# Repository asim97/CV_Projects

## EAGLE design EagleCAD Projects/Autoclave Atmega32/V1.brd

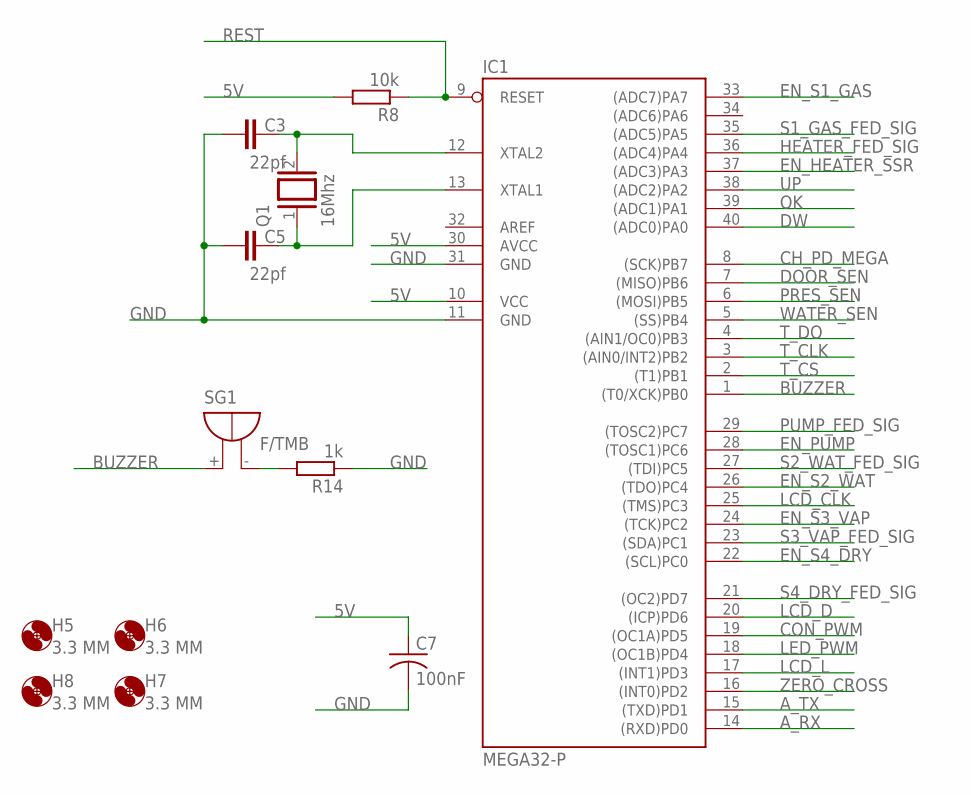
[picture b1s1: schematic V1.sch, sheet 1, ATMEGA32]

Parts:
C3, C5: 22pf; C050-030X075
C7: 100nF; C050-035X075
H5, H6, H7, H8: 3.3 MM; 3,3
IC1: MEGA32-P; DIL40
Q1: 16Mhz; QS
R8: 10k; 0207/10
R14: 1k; 0207/10
SG1: F/TMB

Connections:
5V: C7.1, IC1.10 (VCC), IC1.30 (AVCC), R8.2; also elsewhere on the board
A_RX: IC1.14 ((RXD)PD0); also elsewhere on the board
A_TX: IC1.15 ((TXD)PD1); also elsewhere on the board
BUZZER: IC1.1 ((T0/XCK)PB0), SG1.+
CH_PD_MEGA: IC1.8 ((SCK)PB7); also elsewhere on the board
CON_PWM: IC1.19 ((OC1A)PD5); also elsewhere on the board
DOOR_SEN: IC1.7 ((MISO)PB6); also elsewhere on the board
DW: IC1.40 ((ADC0)PA0); also elsewhere on the board
EN_HEATER_SSR: IC1.37 ((ADC3)PA3); also elsewhere on the board
EN_PUMP: IC1.28 ((TOSC1)PC6); also elsewhere on the board
EN_S1_GAS: IC1.33 ((ADC7)PA7); also elsewhere on the board
EN_S2_WAT: IC1.26 ((TDO)PC4); also elsewhere on the board
EN_S3_VAP: IC1.24 ((TCK)PC2); also elsewhere on the board
EN_S4_DRY: IC1.22 ((SCL)PC0); also elsewhere on the board
GND: C3.1, C5.1, C7.2, IC1.11 (GND), IC1.31 (GND), R14.1; also elsewhere on the board
HEATER_FED_SIG: IC1.36 ((ADC4)PA4); also elsewhere on the board
LCD_CLK: IC1.25 ((TMS)PC3); also elsewhere on the board
LCD_D: IC1.20 ((ICP)PD6); also elsewhere on the board
LCD_L: IC1.17 ((INT1)PD3); also elsewhere on the board
LED_PWM: IC1.18 ((OC1B)PD4); also elsewhere on the board
unnamed: C5.2, IC1.13 (XTAL1), Q1.1
unnamed: C3.2, IC1.12 (XTAL2), Q1.2
unnamed: R14.2, SG1.-
OK: IC1.39 ((ADC1)PA1); also elsewhere on the board
PRES_SEN: IC1.6 ((MOSI)PB5); also elsewhere on the board
PUMP_FED_SIG: IC1.29 ((TOSC2)PC7); also elsewhere on the board
REST: IC1.9 (RESET), R8.1; also elsewhere on the board
S1_GAS_FED_SIG: IC1.35 ((ADC5)PA5); also elsewhere on the board
S2_WAT_FED_SIG: IC1.27 ((TDI)PC5); also elsewhere on the board
S3_VAP_FED_SIG: IC1.23 ((SDA)PC1); also elsewhere on the board
S4_DRY_FED_SIG: IC1.21 ((OC2)PD7); also elsewhere on the board
T_CLK: IC1.3 ((AIN0/INT2)PB2); also elsewhere on the board
T_CS: IC1.2 ((T1)PB1); also elsewhere on the board
T_DO: IC1.4 ((AIN1/OC0)PB3); also elsewhere on the board
UP: IC1.38 ((ADC2)PA2); also elsewhere on the board
WATER_SEN: IC1.5 ((SS)PB4); also elsewhere on the board
ZERO_CROSS: IC1.16 ((INT0)PD2); also elsewhere on the board

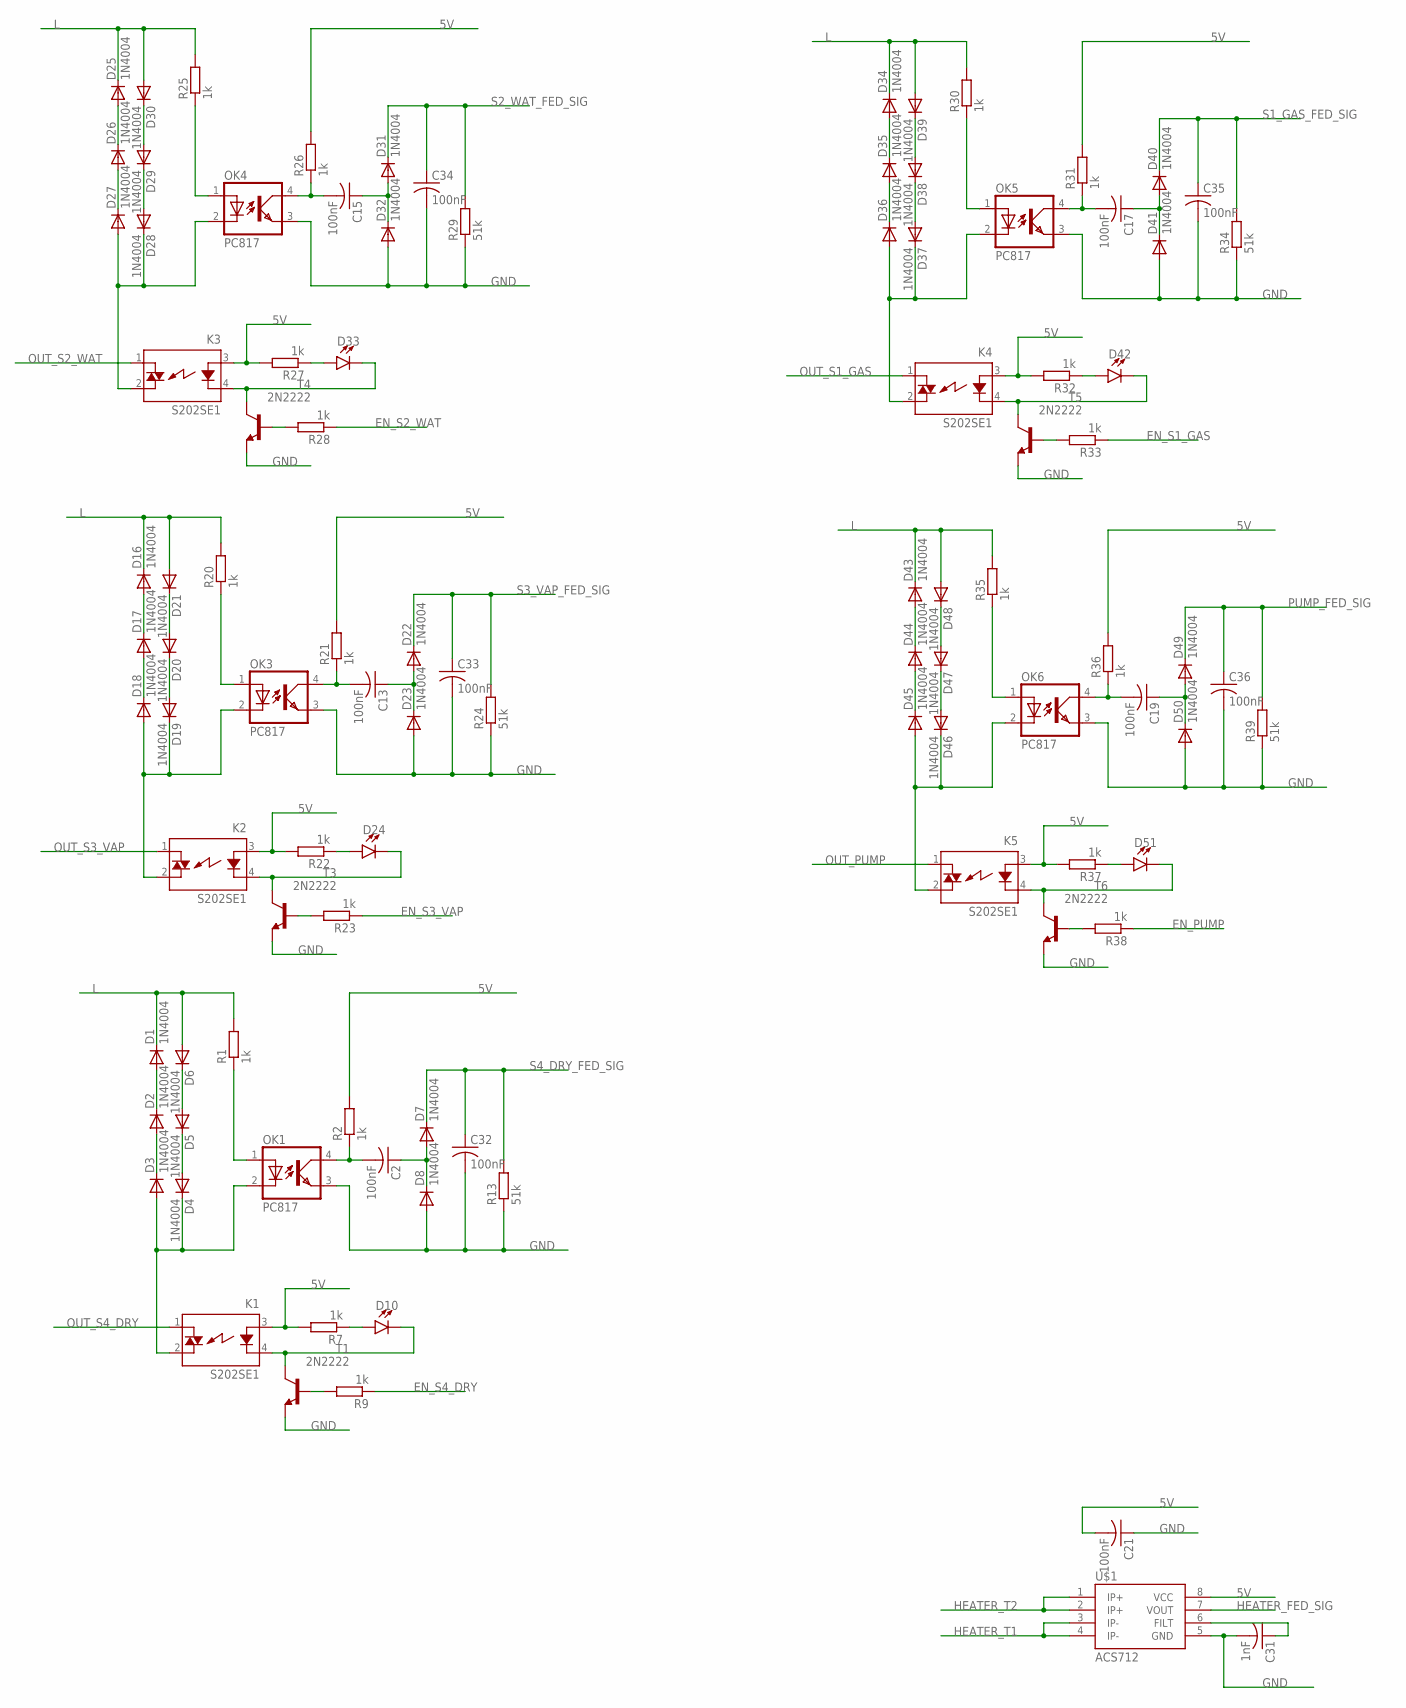
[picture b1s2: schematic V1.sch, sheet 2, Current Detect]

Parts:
C2, C13, C15, C17, C19, C21, C32, C33, C34, C35, C36: 100nF; C050-035X075
C31: 1nF; C050-035X075
D1, D2, D3, D4, D5, D6, D7, D8, D16, D17, D18, D19, D20, D21, D22, D23, D25, D26, D27, D28, D29, D30, D31, D32, D34, D35, D36, D37, D38, D39, D40, D41, D43, D44, D45, D46, D47, D48, D49, D50: 1N4004; DO41-10
D10, D24, D33, D42, D51: LED5MM; LED_5MM
K1, K2, K3, K4, K5: S202SE1; S2XXEX
OK1, OK3, OK4, OK5, OK6: PC817; DIL04
R1, R2, R7, R9, R20, R21, R22, R23, R25, R26, R27, R28, R30, R31, R32, R33, R35, R36, R37, R38: 1k; 0207/10
R13, R24, R29, R34, R39: 51k; 0207/10
T1, T3, T4, T5, T6: 2N2222; TO92-EBC-OVAL
U$1: ACS712; SO08

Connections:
5V: C21.2, K1.3 (A), K2.3 (A), K3.3 (A), K4.3 (A), K5.3 (A), R2.2, R7.2, R21.2, R22.2, R26.2, R27.2, R31.2, R32.2, R36.2, R37.2, U$1.8 (VCC); also elsewhere on the board
EN_PUMP: R38.1; also elsewhere on the board
EN_S1_GAS: R33.1; also elsewhere on the board
EN_S2_WAT: R28.1; also elsewhere on the board
EN_S3_VAP: R23.1; also elsewhere on the board
EN_S4_DRY: R9.1; also elsewhere on the board
GND: C21.1, C31.2, C32.2, C33.2, C34.2, C35.2, C36.2, D8.A, D23.A, D32.A, D41.A, D50.A, OK1.3 (EMIT), OK3.3 (EMIT), OK4.3 (EMIT), OK5.3 (EMIT), OK6.3 (EMIT), R13.1, R24.1, R29.1, R34.1, R39.1, T1.E, T3.E, T4.E, T5.E, T6.E, U$1.5 (GND); also elsewhere on the board
HEATER_FED_SIG: U$1.7 (VOUT); also elsewhere on the board
HEATER_T1: U$1.3 (IP-), U$1.4 (IP-); also elsewhere on the board
HEATER_T2: U$1.1 (IP+), U$1.2 (IP+); also elsewhere on the board
L: D1.C, D6.A, D16.C, D21.A, D25.C, D30.A, D34.C, D39.A, D43.C, D48.A, R1.2, R20.2, R25.2, R30.2, R35.2; also elsewhere on the board
unnamed: D2.A, D3.C
unnamed: D1.A, D2.C
unnamed: C2.2, OK1.4 (COL), R2.1
unnamed: C2.1, D7.A, D8.C
unnamed: D5.A, D6.C
unnamed: D4.A, D5.C
unnamed: D10.K (C), K1.4 (K), T1.C
unnamed: OK1.1 (A), R1.1
unnamed: D17.A, D18.C
unnamed: D10.A, R7.1
unnamed: R9.2, T1.B
unnamed: D3.A, D4.C, K1.2 (DS2), OK1.2 (C)
unnamed: D16.A, D17.C
unnamed: D20.A, D21.C
unnamed: D19.A, D20.C
unnamed: OK3.1 (A), R20.1
unnamed: C13.2, OK3.4 (COL), R21.1
unnamed: C13.1, D22.A, D23.C
unnamed: D18.A, D19.C, K2.2 (DS2), OK3.2 (C)
unnamed: D24.A, R22.1
unnamed: D24.K (C), K2.4 (K), T3.C
unnamed: R23.2, T3.B
unnamed: D26.A, D27.C
unnamed: D25.A, D26.C
unnamed: D29.A, D30.C
unnamed: D28.A, D29.C
unnamed: OK4.1 (A), R25.1
unnamed: C15.2, OK4.4 (COL), R26.1
unnamed: C15.1, D31.A, D32.C
unnamed: D27.A, D28.C, K3.2 (DS2), OK4.2 (C)
unnamed: D33.A, R27.1
unnamed: D33.K (C), K3.4 (K), T4.C
unnamed: R28.2, T4.B
unnamed: D35.A, D36.C
unnamed: D34.A, D35.C
unnamed: D38.A, D39.C
unnamed: D37.A, D38.C
unnamed: OK5.1 (A), R30.1
unnamed: C17.2, OK5.4 (COL), R31.1
unnamed: C17.1, D40.A, D41.C
unnamed: D36.A, D37.C, K4.2 (DS2), OK5.2 (C)
unnamed: D42.A, R32.1
unnamed: D42.K (C), K4.4 (K), T5.C
unnamed: R33.2, T5.B
unnamed: D44.A, D45.C
unnamed: D43.A, D44.C
unnamed: D47.A, D48.C
unnamed: D46.A, D47.C
unnamed: OK6.1 (A), R35.1
unnamed: C19.2, OK6.4 (COL), R36.1
unnamed: C19.1, D49.A, D50.C
unnamed: D45.A, D46.C, K5.2 (DS2), OK6.2 (C)
unnamed: D51.A, R37.1
unnamed: D51.K (C), K5.4 (K), T6.C
unnamed: R38.2, T6.B
unnamed: C31.1, U$1.6 (FILT)
OUT_PUMP: K5.1 (DS1); also elsewhere on the board
OUT_S1_GAS: K4.1 (DS1); also elsewhere on the board
OUT_S2_WAT: K3.1 (DS1); also elsewhere on the board
OUT_S3_VAP: K2.1 (DS1); also elsewhere on the board
OUT_S4_DRY: K1.1 (DS1); also elsewhere on the board
PUMP_FED_SIG: C36.1, D49.C, R39.2; also elsewhere on the board
S1_GAS_FED_SIG: C35.1, D40.C, R34.2; also elsewhere on the board
S2_WAT_FED_SIG: C34.1, D31.C, R29.2; also elsewhere on the board
S3_VAP_FED_SIG: C33.1, D22.C, R24.2; also elsewhere on the board
S4_DRY_FED_SIG: C32.1, D7.C, R13.2; also elsewhere on the board

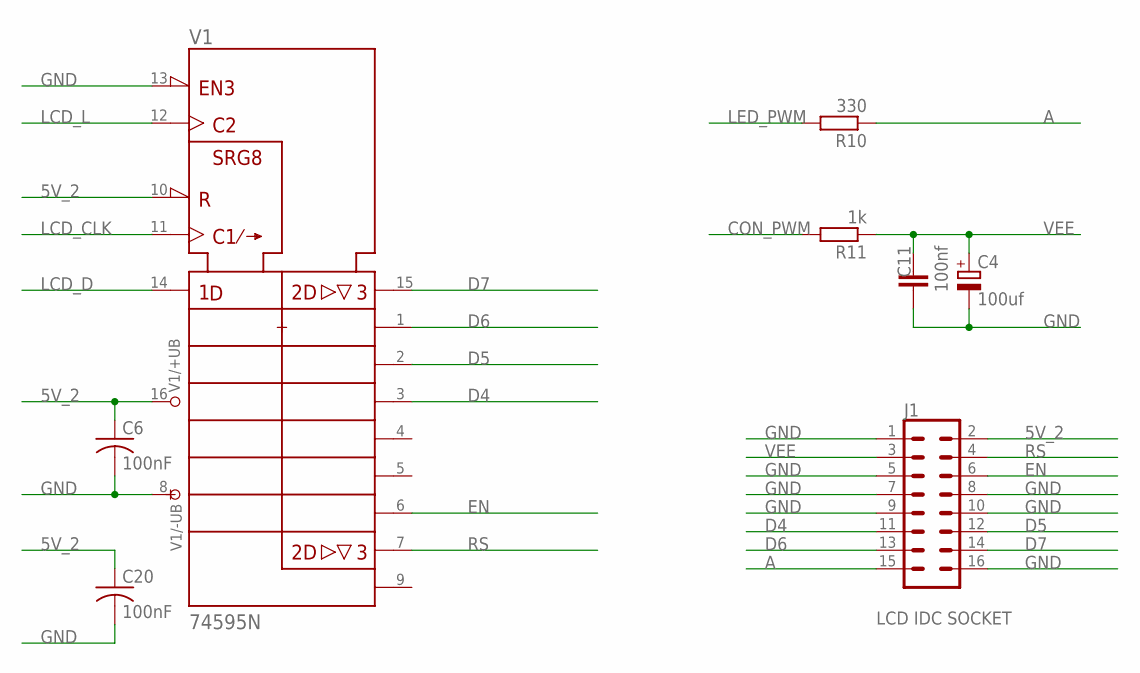
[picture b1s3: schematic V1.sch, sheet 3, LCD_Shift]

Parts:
C4: 100uf; E3,5-8
C6, C20: 100nF; C050-035X075
C11: 100nf; C050-030X075
J1: CONN_08X2; 2X8
R10: 330; 0207/10
R11: 1k; 0207/10
V1: 74595N; DIL16

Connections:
5V_2: C6.1, C20.1, J1.2, V1.10 (!SRCLR), V1.16 (+UB); also elsewhere on the board
A: J1.15, R10.1
CON_PWM: R11.2; also elsewhere on the board
D4: J1.11, V1.3 (QD)
D5: J1.12, V1.2 (QC)
D6: J1.13, V1.1 (QB)
D7: J1.14, V1.15 (QA)
EN: J1.6, V1.6 (QG)
GND: C4.-, C6.2, C11.1, C20.2, J1.1, J1.5, J1.7, J1.8, J1.9, J1.10, J1.16, V1.8 (-UB), V1.13 (!G); also elsewhere on the board
LCD_CLK: V1.11 (SRCK); also elsewhere on the board
LCD_D: V1.14 (SER); also elsewhere on the board
LCD_L: V1.12 (RCK); also elsewhere on the board
LED_PWM: R10.2; also elsewhere on the board
RS: J1.4, V1.7 (QH)
VEE: C4.+, C11.2, J1.3, R11.1

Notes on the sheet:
LCD IDC SOCKET

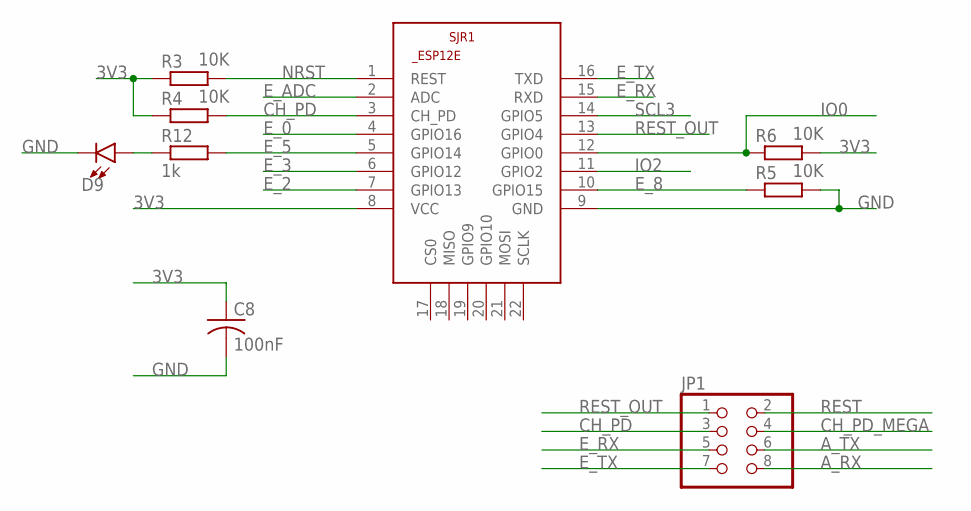
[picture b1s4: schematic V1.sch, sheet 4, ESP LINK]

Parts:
C8: 100nF; C050-035X075
D9: LED5MM; LED_5MM
JP1: PINHD-2X4; 2X04
R3, R4, R5, R6: 10K; 0207/10
R12: 1k; 0207/10
SJR1: ESP8266-12EESP12E; ESP8266-ESP12E

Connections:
3V3: C8.1, R3.1, R4.1, R6.2, SJR1.8 (VCC); also elsewhere on the board
A_RX: JP1.8; also elsewhere on the board
A_TX: JP1.6; also elsewhere on the board
CH_PD: JP1.3, R4.2, SJR1.3 (CH_PD)
CH_PD_MEGA: JP1.4; also elsewhere on the board
E_0: SJR1.4 (GPIO16)
E_2: SJR1.7 (GPIO13)
E_3: SJR1.6 (GPIO12)
E_5: R12.2, SJR1.5 (GPIO14)
E_8: R5.1, SJR1.10 (GPIO15)
E_ADC: SJR1.2 (ADC)
E_RX: JP1.5, SJR1.15 (RXD)
E_TX: JP1.7, SJR1.16 (TXD)
GND: C8.2, D9.K (C), R5.2, SJR1.9 (GND); also elsewhere on the board
IO0: R6.1, SJR1.12 (GPIO0)
IO2: SJR1.11 (GPIO2)
unnamed: D9.A, R12.1
NRST: R3.2, SJR1.1 (REST)
REST: JP1.2; also elsewhere on the board
REST_OUT: JP1.1, SJR1.13 (GPIO4)
SCL3: SJR1.14 (GPIO5)

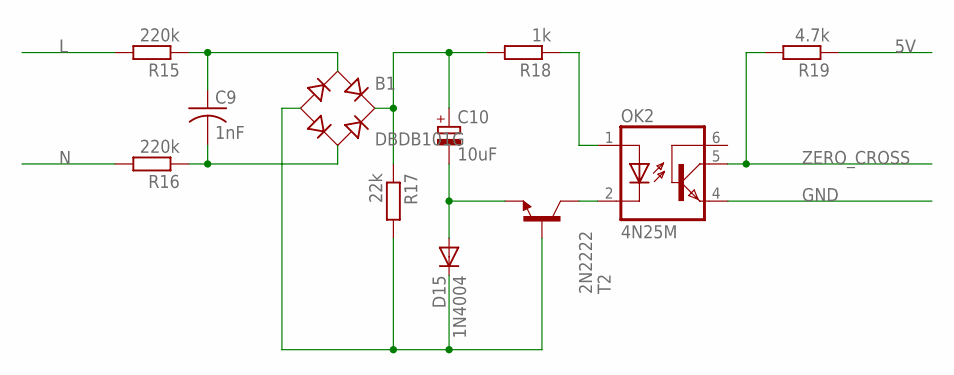
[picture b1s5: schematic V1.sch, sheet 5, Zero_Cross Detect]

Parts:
B1: DBDB101G; DB
C9: 1nF; C050-035X075
C10: 10uF; E2,5-7
D15: 1N4004; DO41-10
OK2: 4N25M; DIL06
R15, R16: 220k; 0207/10
R17: 22k; 0207/10
R18: 1k; 0207/10
R19: 4.7k; 0207/10
T2: 2N2222; TO92-EBC-OVAL

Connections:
5V: R19.1; also elsewhere on the board
GND: OK2.4 (EMI); also elsewhere on the board
L: R15.2; also elsewhere on the board
N: R16.2; also elsewhere on the board
unnamed: B1.AC2, C9.2, R16.1
unnamed: B1.AC1, C9.1, R15.1
unnamed: B1.+, C10.+, R17.1, R18.2
unnamed: B1.-, D15.C, R17.2, T2.B
unnamed: C10.-, D15.A, T2.E
unnamed: OK2.2 (C), T2.C
unnamed: OK2.1 (A), R18.1
ZERO_CROSS: OK2.5 (COL), R19.2; also elsewhere on the board

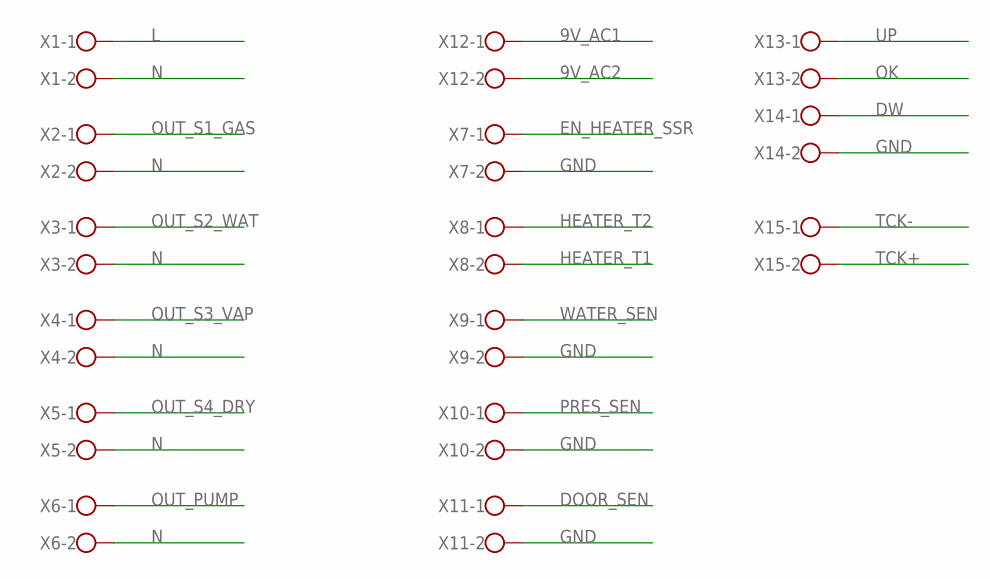
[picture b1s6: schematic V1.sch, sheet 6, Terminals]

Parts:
X1, X2, X3, X4, X5, X6, X7, X8, X9, X10, X11, X12, X13, X14, X15: W237-102

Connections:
9V_AC1: X12.1; also elsewhere on the board
9V_AC2: X12.2; also elsewhere on the board
DOOR_SEN: X11.1; also elsewhere on the board
DW: X14.1; also elsewhere on the board
EN_HEATER_SSR: X7.1; also elsewhere on the board
GND: X7.2, X9.2, X10.2, X11.2, X14.2; also elsewhere on the board
HEATER_T1: X8.2; also elsewhere on the board
HEATER_T2: X8.1; also elsewhere on the board
L: X1.1; also elsewhere on the board
N: X1.2, X2.2, X3.2, X4.2, X5.2, X6.2; also elsewhere on the board
OK: X13.2; also elsewhere on the board
OUT_PUMP: X6.1; also elsewhere on the board
OUT_S1_GAS: X2.1; also elsewhere on the board
OUT_S2_WAT: X3.1; also elsewhere on the board
OUT_S3_VAP: X4.1; also elsewhere on the board
OUT_S4_DRY: X5.1; also elsewhere on the board
PRES_SEN: X10.1; also elsewhere on the board
TCK+: X15.2; also elsewhere on the board
TCK-: X15.1; also elsewhere on the board
UP: X13.1; also elsewhere on the board
WATER_SEN: X9.1; also elsewhere on the board

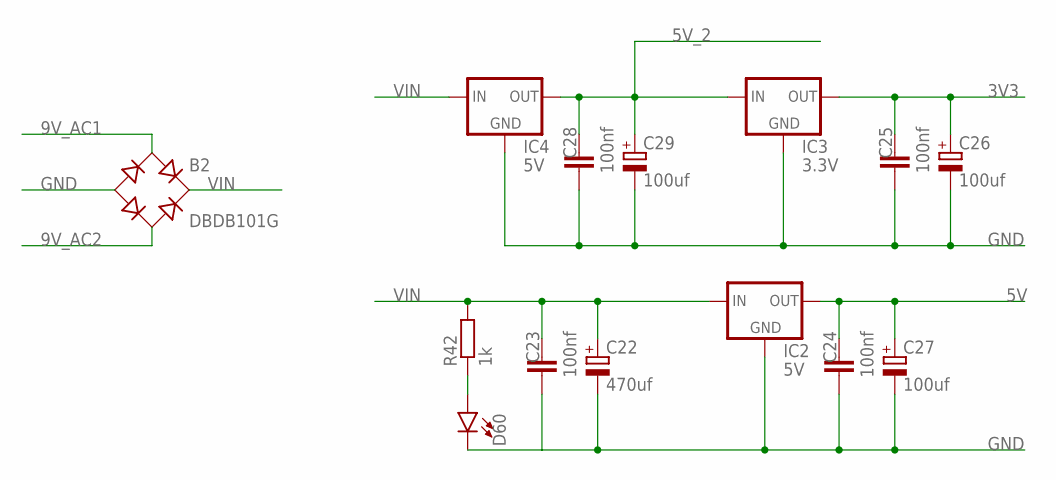
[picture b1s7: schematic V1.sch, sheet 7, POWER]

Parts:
B2: DBDB101G; DB
C22: 470uf; E3,5-8
C23, C24, C25, C28: 100nf; C050-030X075
C26, C27, C29: 100uf; E3,5-8
D60: LED5MM; LED_5MM
IC2, IC4: 5V; 78XXL
IC3: 3.3V; 78XXL
R42: 1k; 0207/10

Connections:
3V3: C25.2, C26.+, IC3.OUT; also elsewhere on the board
5V: C24.2, C27.+, IC2.OUT; also elsewhere on the board
5V_2: C28.2, C29.+, IC3.IN, IC4.OUT; also elsewhere on the board
9V_AC1: B2.AC1; also elsewhere on the board
9V_AC2: B2.AC2; also elsewhere on the board
GND: B2.-, C22.-, C23.1, C24.1, C25.1, C26.-, C27.-, C28.1, C29.-, D60.K (C), IC2.GND, IC3.GND, IC4.GND; also elsewhere on the board
unnamed: D60.A, R42.1
VIN: B2.+, C22.+, C23.2, IC2.IN, IC4.IN, R42.2

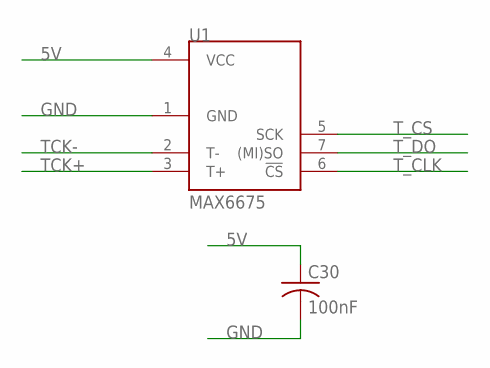
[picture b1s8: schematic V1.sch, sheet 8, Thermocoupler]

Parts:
C30: 100nF; C050-035X075
U1: MAX6675; SOIC8

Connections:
5V: C30.1, U1.4 (VCC); also elsewhere on the board
GND: C30.2, U1.1 (GND); also elsewhere on the board
TCK+: U1.3 (T+); also elsewhere on the board
TCK-: U1.2 (T-); also elsewhere on the board
T_CLK: U1.6 (!CS); also elsewhere on the board
T_CS: U1.5 (SCK); also elsewhere on the board
T_DO: U1.7 ((MI)SO); also elsewhere on the board

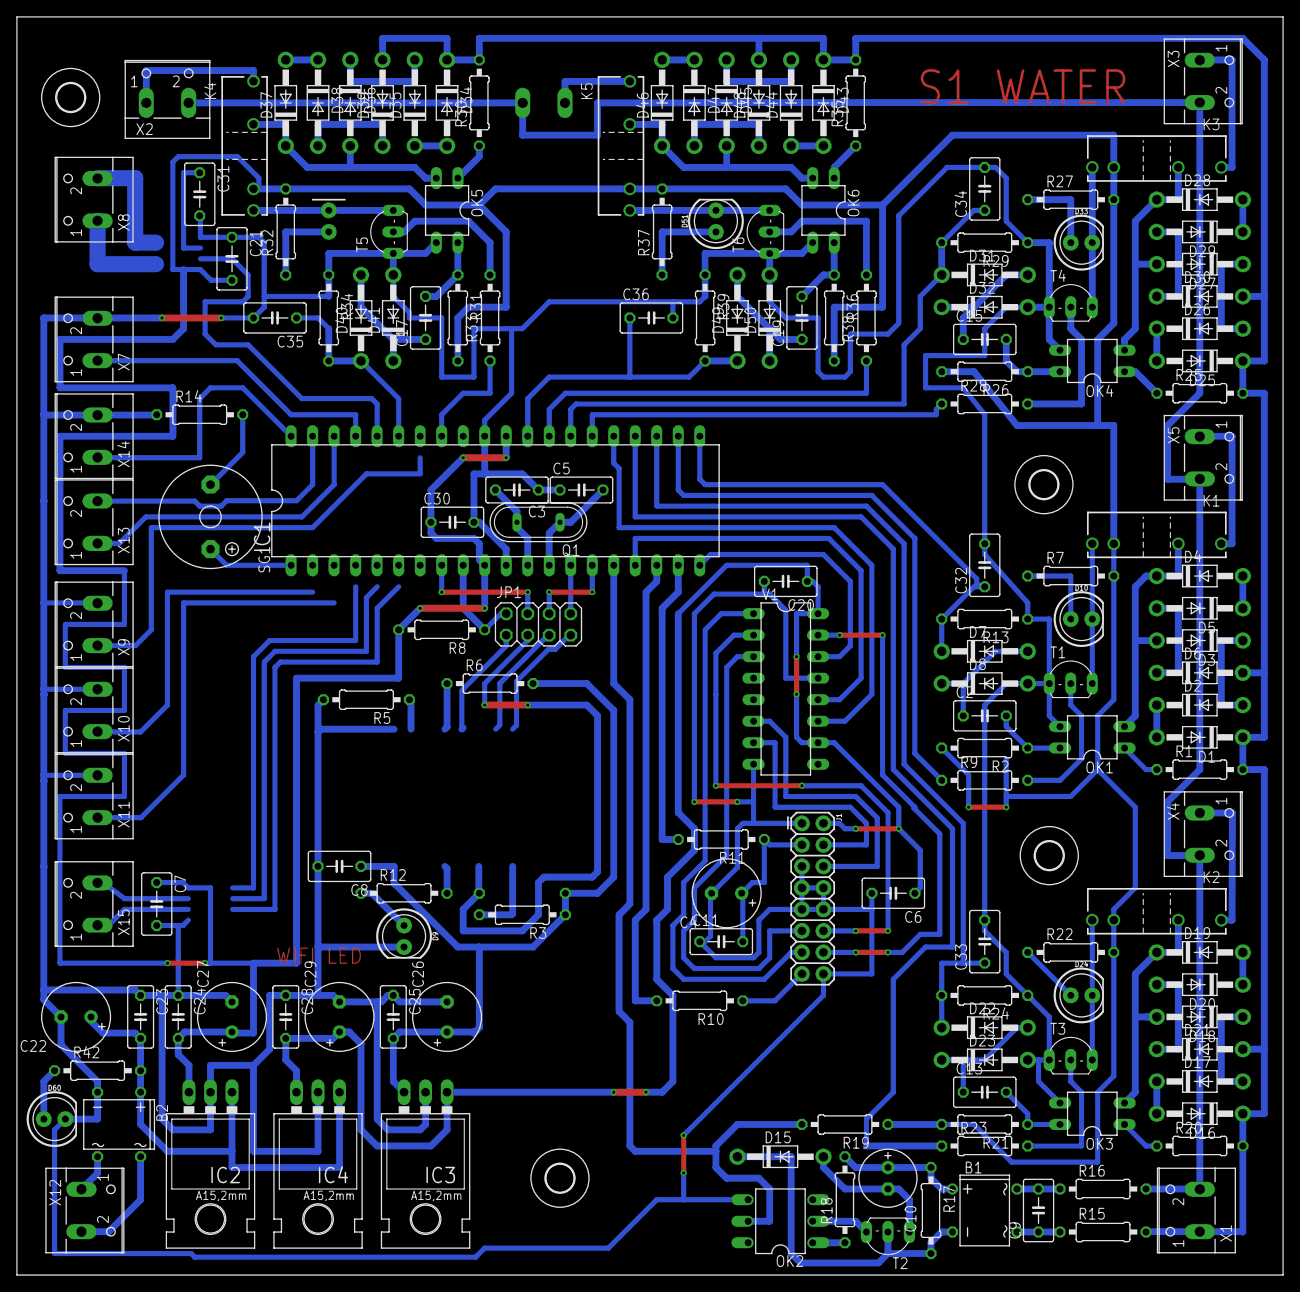
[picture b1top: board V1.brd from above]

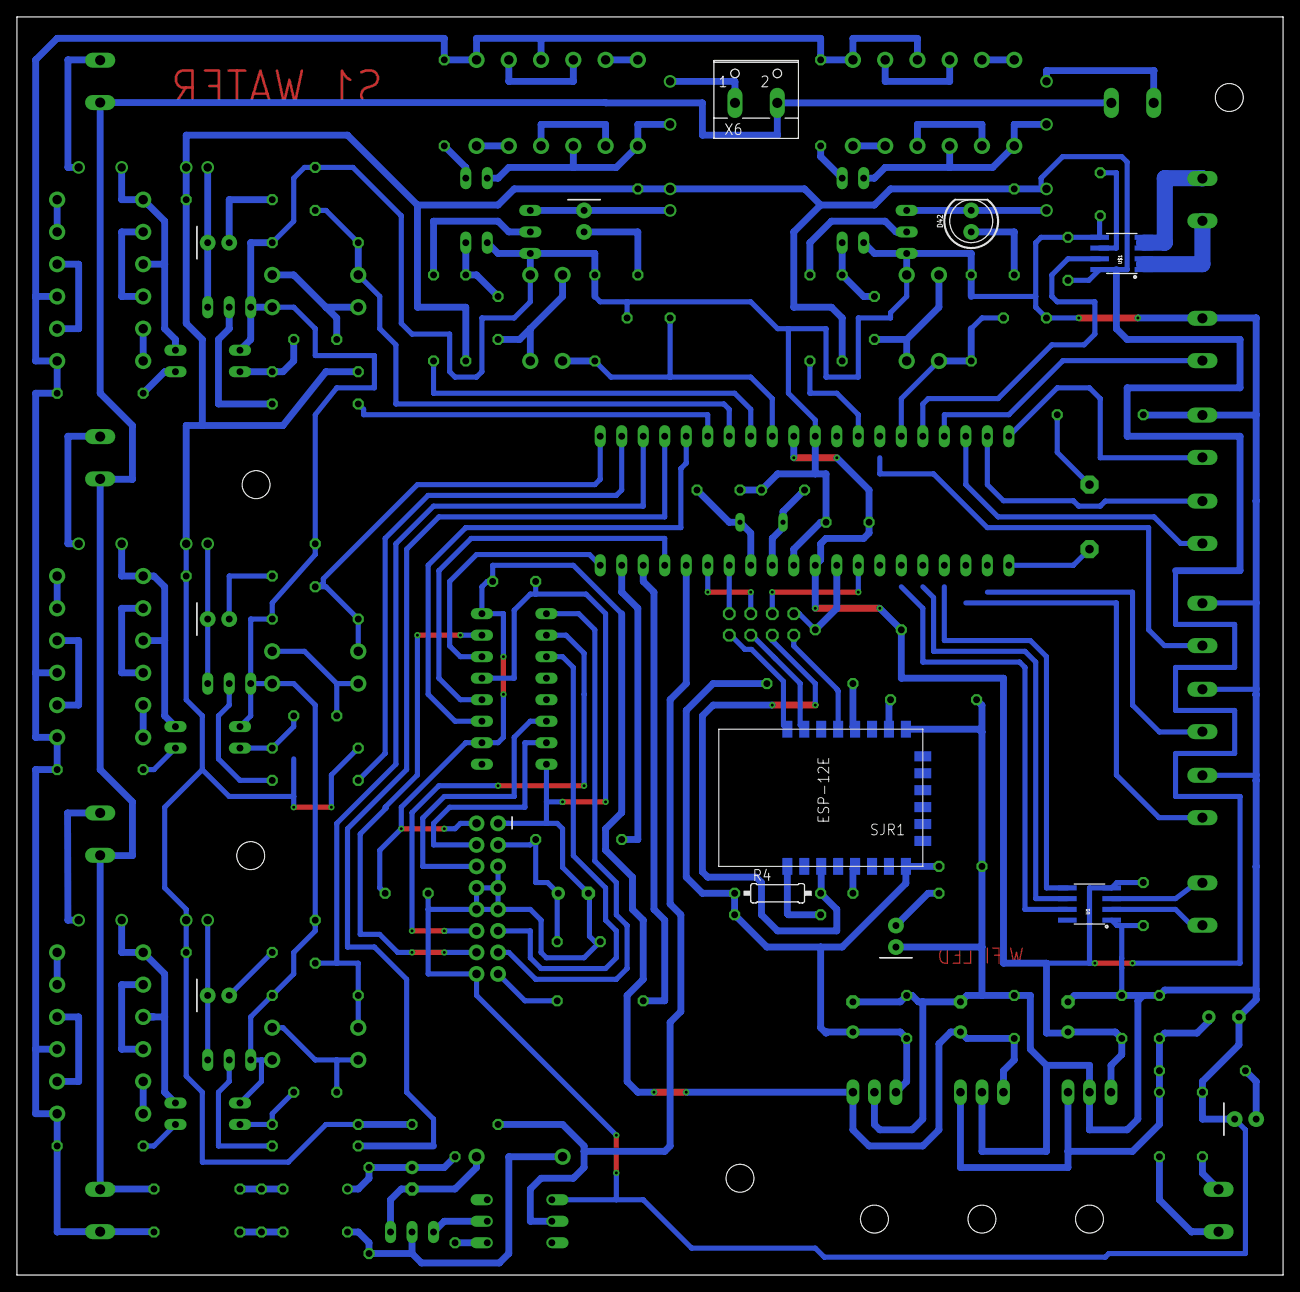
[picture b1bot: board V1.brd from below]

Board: 2 copper layers, 149.5 x 148.6 mm, 169 parts (6 on the bottom side), 134 nets.

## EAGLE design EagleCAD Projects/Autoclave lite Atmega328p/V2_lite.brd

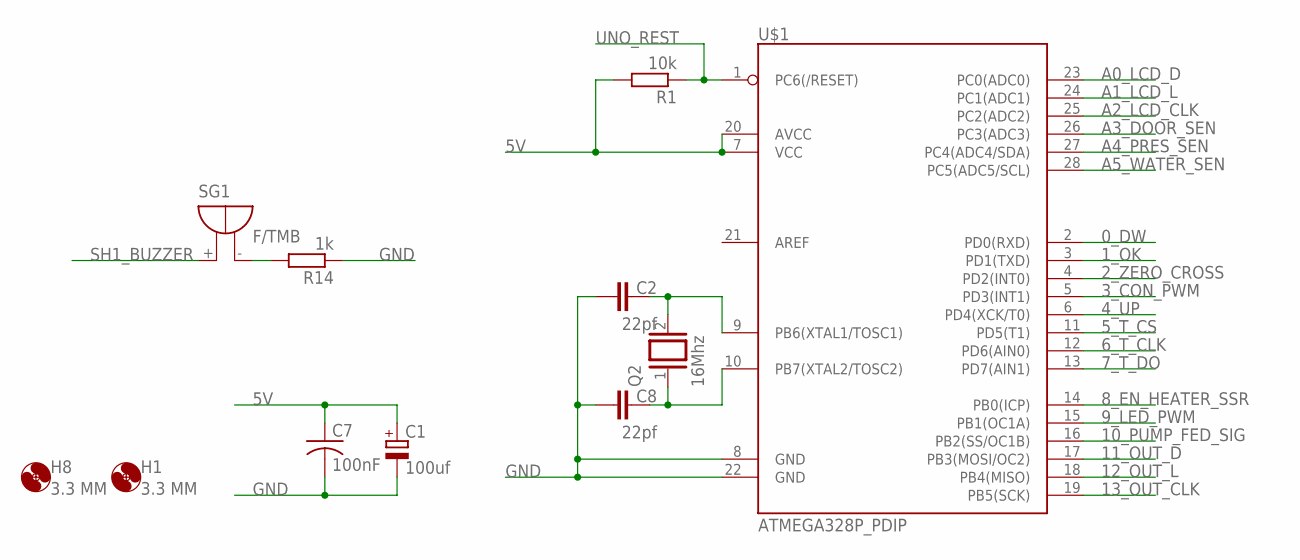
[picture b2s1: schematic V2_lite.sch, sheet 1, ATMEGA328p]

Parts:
C1: 100uf; E3,5-8
C2, C8: 22pf; C050-030X075
C7: 100nF; C050-035X075
H1, H8: 3.3 MM; 3,3
Q2: 16Mhz; QS
R1: 10k; 0207/10
R14: 1k; 0207/10
SG1: F/TMB
U$1: ATMEGA328P_PDIP; DIL-28-3

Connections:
0_DW: U$1.2 (PD0(RXD)); also elsewhere on the board
1_OK: U$1.3 (PD1(TXD)); also elsewhere on the board
2_ZERO_CROSS: U$1.4 (PD2(INT0)); also elsewhere on the board
3_CON_PWM: U$1.5 (PD3(INT1)); also elsewhere on the board
4_UP: U$1.6 (PD4(XCK/T0)); also elsewhere on the board
5V: C1.+, C7.1, R1.2, U$1.7 (VCC), U$1.20 (AVCC); also elsewhere on the board
5_T_CS: U$1.11 (PD5(T1)); also elsewhere on the board
6_T_CLK: U$1.12 (PD6(AIN0)); also elsewhere on the board
7_T_DO: U$1.13 (PD7(AIN1)); also elsewhere on the board
8_EN_HEATER_SSR: U$1.14 (PB0(ICP)); also elsewhere on the board
9_LED_PWM: U$1.15 (PB1(OC1A)); also elsewhere on the board
10_PUMP_FED_SIG: U$1.16 (PB2(SS/OC1B)); also elsewhere on the board
11_OUT_D: U$1.17 (PB3(MOSI/OC2)); also elsewhere on the board
12_OUT_L: U$1.18 (PB4(MISO)); also elsewhere on the board
13_OUT_CLK: U$1.19 (PB5(SCK)); also elsewhere on the board
A0_LCD_D: U$1.23 (PC0(ADC0)); also elsewhere on the board
A1_LCD_L: U$1.24 (PC1(ADC1)); also elsewhere on the board
A2_LCD_CLK: U$1.25 (PC2(ADC2)); also elsewhere on the board
A3_DOOR_SEN: U$1.26 (PC3(ADC3)); also elsewhere on the board
A4_PRES_SEN: U$1.27 (PC4(ADC4/SDA)); also elsewhere on the board
A5_WATER_SEN: U$1.28 (PC5(ADC5/SCL)); also elsewhere on the board
GND: C1.-, C2.1, C7.2, C8.1, R14.1, U$1.8 (GND), U$1.22 (GND); also elsewhere on the board
unnamed: C2.2, Q2.2, U$1.9 (PB6(XTAL1/TOSC1))
unnamed: C8.2, Q2.1, U$1.10 (PB7(XTAL2/TOSC2))
unnamed: R14.2, SG1.-
SH1_BUZZER: SG1.+; also elsewhere on the board
UNO_REST: R1.1, U$1.1 (PC6(/RESET))

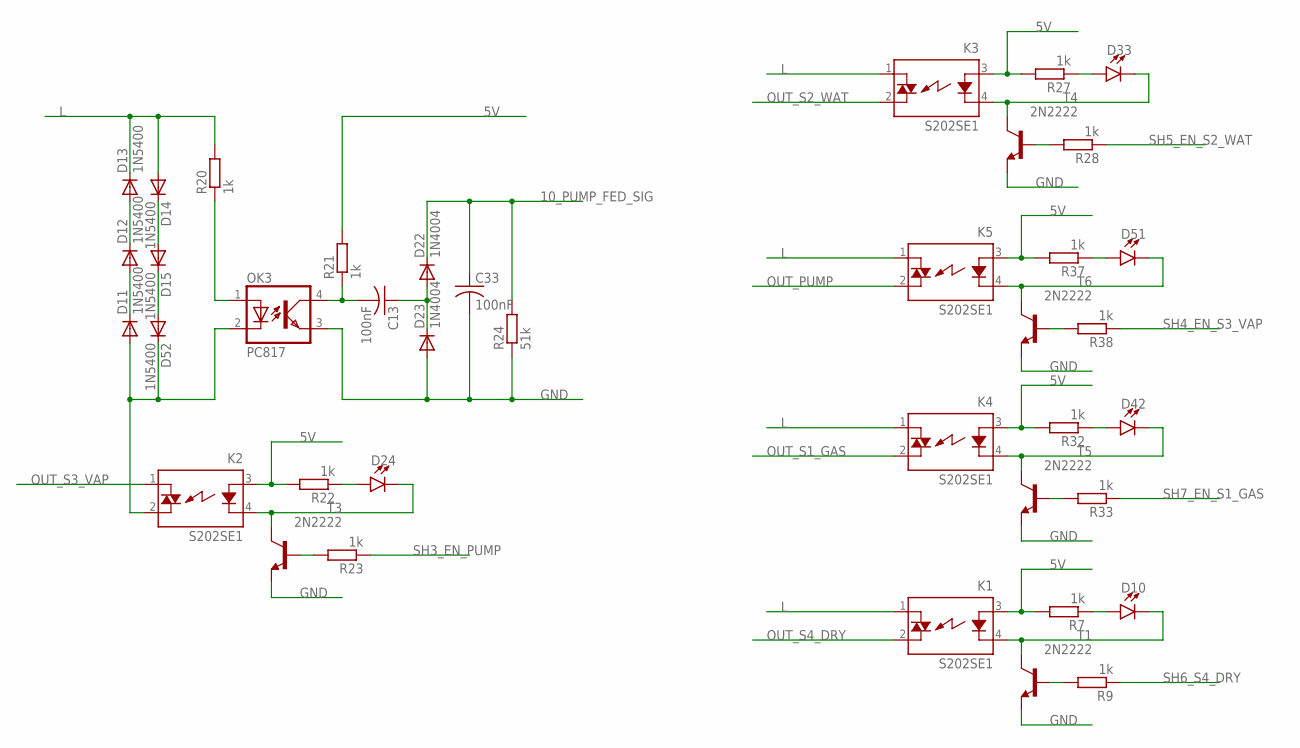
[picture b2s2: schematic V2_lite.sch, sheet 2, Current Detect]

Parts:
C13, C33: 100nF; C050-035X075
D10, D24, D33, D42, D51: LED5MM; LED_5MM
D11, D12, D13, D14, D15, D52: 1N5400; DO201-15
D22, D23: 1N4004; DO41-10
K1, K2, K3, K4, K5: S202SE1; S2XXEX
OK3: PC817; DIL04
R7, R9, R20, R21, R22, R23, R27, R28, R32, R33, R37, R38: 1k; 0207/10
R24: 51k; 0207/10
T1, T3, T4, T5, T6: 2N2222; TO92-EBC-OVAL

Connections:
5V: K1.3 (A), K2.3 (A), K3.3 (A), K4.3 (A), K5.3 (A), R7.2, R21.2, R22.2, R27.2, R32.2, R37.2; also elsewhere on the board
10_PUMP_FED_SIG: C33.1, D22.C, R24.2; also elsewhere on the board
GND: C33.2, D23.A, OK3.3 (EMIT), R24.1, T1.E, T3.E, T4.E, T5.E, T6.E; also elsewhere on the board
L: D13.C, D14.A, K1.1 (DS1), K3.1 (DS1), K4.1 (DS1), K5.1 (DS1), R20.2; also elsewhere on the board
unnamed: D10.K (C), K1.4 (K), T1.C
unnamed: D11.C, D12.A
unnamed: D10.A, R7.1
unnamed: R9.2, T1.B
unnamed: D12.C, D13.A
unnamed: D14.C, D15.A
unnamed: D15.C, D52.A
unnamed: OK3.1 (A), R20.1
unnamed: C13.2, OK3.4 (COL), R21.1
unnamed: C13.1, D22.A, D23.C
unnamed: D24.A, R22.1
unnamed: D24.K (C), K2.4 (K), T3.C
unnamed: R23.2, T3.B
unnamed: D33.A, R27.1
unnamed: D33.K (C), K3.4 (K), T4.C
unnamed: R28.2, T4.B
unnamed: D42.A, R32.1
unnamed: D42.K (C), K4.4 (K), T5.C
unnamed: D11.A, D52.C, K2.2 (DS2), OK3.2 (C)
unnamed: R33.2, T5.B
unnamed: D51.A, R37.1
unnamed: D51.K (C), K5.4 (K), T6.C
unnamed: R38.2, T6.B
OUT_PUMP: K5.2 (DS2); also elsewhere on the board
OUT_S1_GAS: K4.2 (DS2); also elsewhere on the board
OUT_S2_WAT: K3.2 (DS2); also elsewhere on the board
OUT_S3_VAP: K2.1 (DS1); also elsewhere on the board
OUT_S4_DRY: K1.2 (DS2); also elsewhere on the board
SH3_EN_PUMP: R23.1; also elsewhere on the board
SH4_EN_S3_VAP: R38.1; also elsewhere on the board
SH5_EN_S2_WAT: R28.1; also elsewhere on the board
SH6_S4_DRY: R9.1; also elsewhere on the board
SH7_EN_S1_GAS: R33.1; also elsewhere on the board

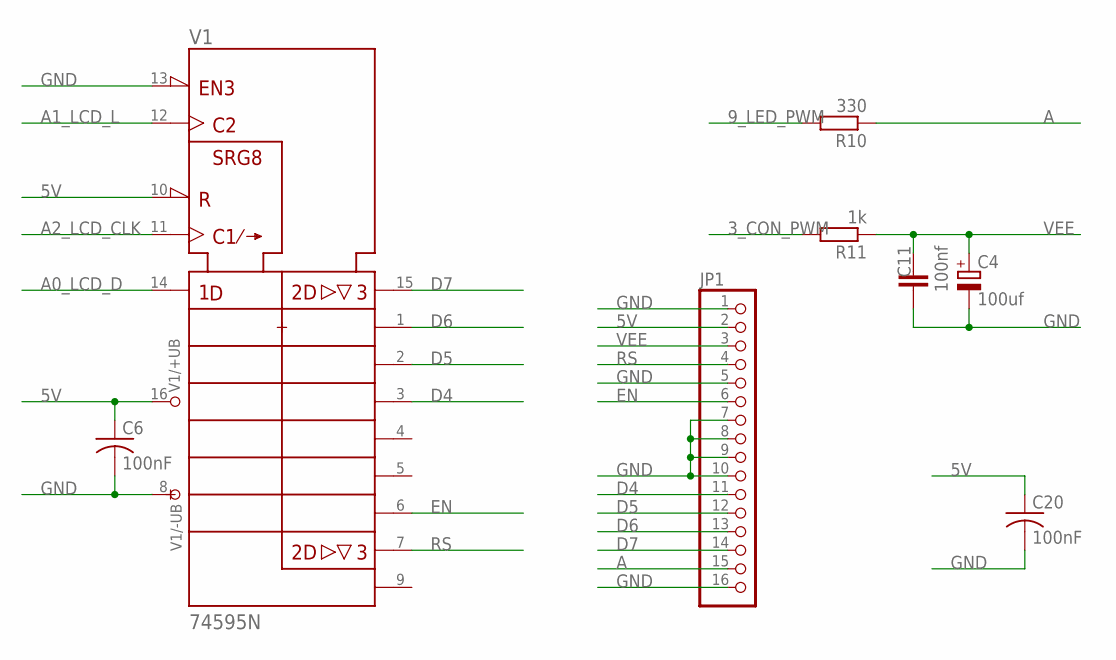
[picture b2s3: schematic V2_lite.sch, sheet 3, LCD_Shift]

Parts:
C4: 100uf; E3,5-8
C6, C20: 100nF; C050-035X075
C11: 100nf; C050-030X075
JP1: PINHD-1X16; 1X16
R10: 330; 0207/10
R11: 1k; 0207/10
V1: 74595N; DIL16

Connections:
3_CON_PWM: R11.2; also elsewhere on the board
5V: C6.1, C20.1, JP1.2, V1.10 (!SRCLR), V1.16 (+UB); also elsewhere on the board
9_LED_PWM: R10.2; also elsewhere on the board
A: JP1.15, R10.1
A0_LCD_D: V1.14 (SER); also elsewhere on the board
A1_LCD_L: V1.12 (RCK); also elsewhere on the board
A2_LCD_CLK: V1.11 (SRCK); also elsewhere on the board
D4: JP1.11, V1.3 (QD)
D5: JP1.12, V1.2 (QC)
D6: JP1.13, V1.1 (QB)
D7: JP1.14, V1.15 (QA)
EN: JP1.6, V1.6 (QG)
GND: C4.-, C6.2, C11.1, C20.2, JP1.1, JP1.5, JP1.7, JP1.8, JP1.9, JP1.10, JP1.16, V1.8 (-UB), V1.13 (!G); also elsewhere on the board
RS: JP1.4, V1.7 (QH)
VEE: C4.+, C11.2, JP1.3, R11.1

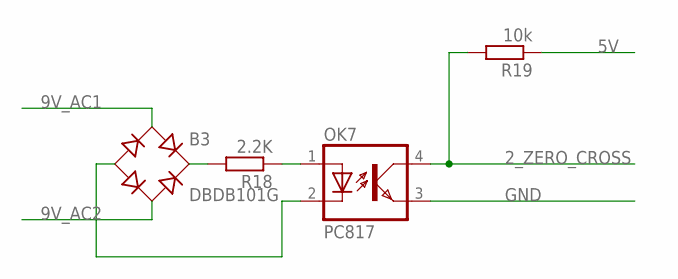
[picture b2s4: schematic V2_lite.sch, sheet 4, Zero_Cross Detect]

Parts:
B3: DBDB101G; DB
OK7: PC817; DIL04
R18: 2.2K; 0207/10
R19: 10k; 0207/10

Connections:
2_ZERO_CROSS: OK7.4 (COL), R19.2; also elsewhere on the board
5V: R19.1; also elsewhere on the board
9V_AC1: B3.AC1; also elsewhere on the board
9V_AC2: B3.AC2; also elsewhere on the board
GND: OK7.3 (EMIT); also elsewhere on the board
unnamed: B3.+, R18.2
unnamed: OK7.1 (A), R18.1
unnamed: B3.-, OK7.2 (C)

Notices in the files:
parts and their libraries:
SparkFun-LED: Licensing: Creative Commons ShareAlike 4.0 International - https://creativecommons.org/licenses/by-sa/4.0
